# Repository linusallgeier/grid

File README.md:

# Grid

Grid is a Scara (Selective compliance assembly robot arm) project build for home-usage.

## Core Features 🚀

- **Inverse Kinematics:** Real-time joint angle and stepper motor position calculation for X/Y coordinates.
- **Graphical UI:** Built-in live arm preview and coordinate selection.
- **Custom Hardware:** A single dual-layer PCB combines logic and power supply.
- **Precise Motion:** Using SilentStepStick TMC 2209 with 16x microstepping for stepper motor control.

## Usage 💻

### Requirements
Ensure your system runs Python 3 and you have the Arduino IDE installed.

### Installation
Install the required dependencies:
```bash
pip install matplotlib pyserial
```

### Getting Started
1. Flash the microcontroller firmware (`stepper_control.ino`) onto the Arduino Nano.
2. Connect your PC to the PCB via micro USB.
3. Update the configuration inside `serial_communication.py` (Default: `/dev/cu.usbmodem11201`).
4. Run the `main.py` program.

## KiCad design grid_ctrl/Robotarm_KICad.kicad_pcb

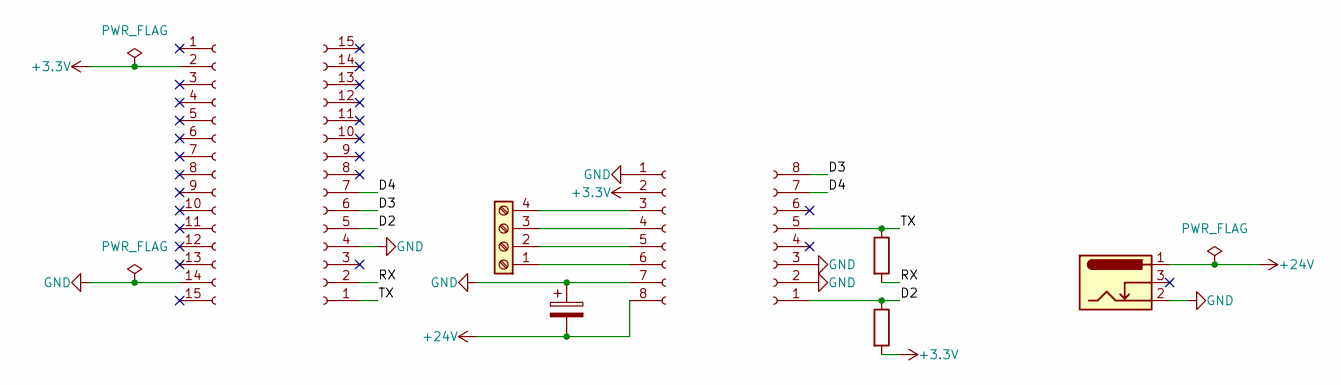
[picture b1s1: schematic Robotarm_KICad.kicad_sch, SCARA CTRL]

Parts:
C2: C_Polarized; CP_Radial_D8.0mm_P3.50mm
J1, J2: Arduino Nano BLE 33 Sense Lite; PinSocket_1x15_P2.54mm_Vertical
J3: Stepper 1; TerminalBlock_Phoenix_MKDS-1,5-4-5.08_1x04_P5.08mm_Horizont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
J4, J5: SilentStepStich TMC2209; PinSocket_1x08_P2.54mm_Vertical
J6: Barrel Jack 24V; BarrelJack_Horizontal
R1: 1k; R_Axial_DIN0309_L9.0mm_D3.2mm_P12.70mm_Horizontal
R2: 10k; R_Axial_DIN0309_L9.0mm_D3.2mm_P12.70mm_Horizontal

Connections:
+3.3V: J1.2, J4.2, R2.2
+24V: C2.2, J4.8, J6.1
/D2: J2.5, J5.1, R2.1
/D3: J2.6, J5.8
/D4: J2.7, J5.7
/RX: J2.2, R1.2
/TX: J2.1, J5.5, R1.1
GND: C2.1, J1.14, J2.4, J4.1, J4.7, J5.2, J5.3, J6.2
unnamed: J3.1, J4.6
unnamed: J3.2, J4.5
unnamed: J3.3, J4.4
unnamed: J3.4, J4.3

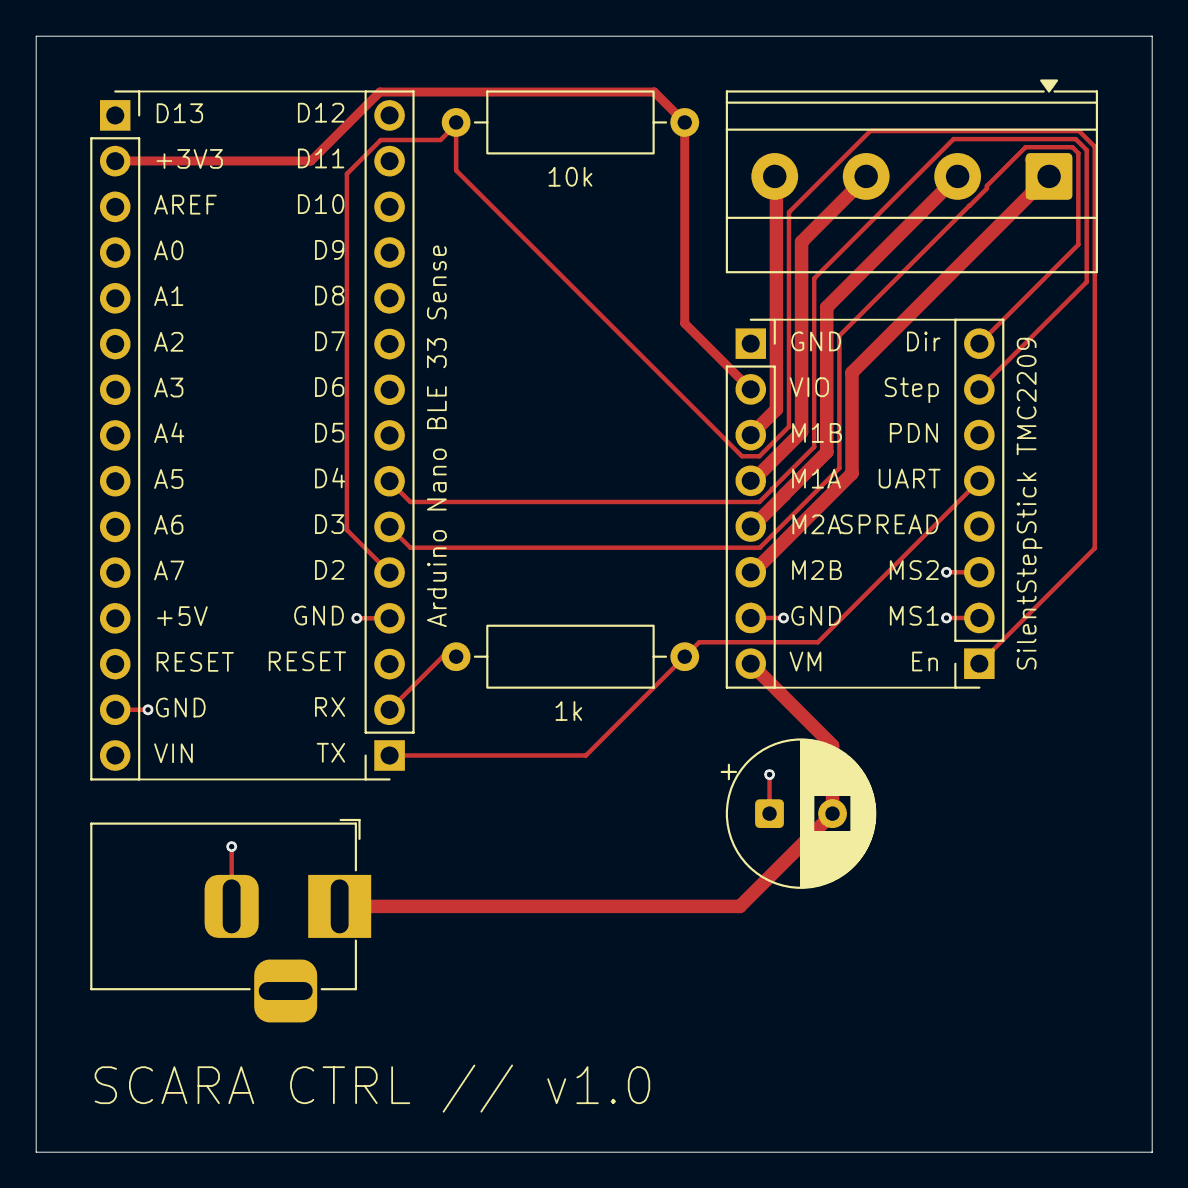
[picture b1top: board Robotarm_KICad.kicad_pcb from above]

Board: 2 copper layers, 62.0 x 62.0 mm, 9 parts (0 on the bottom side), 12 nets.
